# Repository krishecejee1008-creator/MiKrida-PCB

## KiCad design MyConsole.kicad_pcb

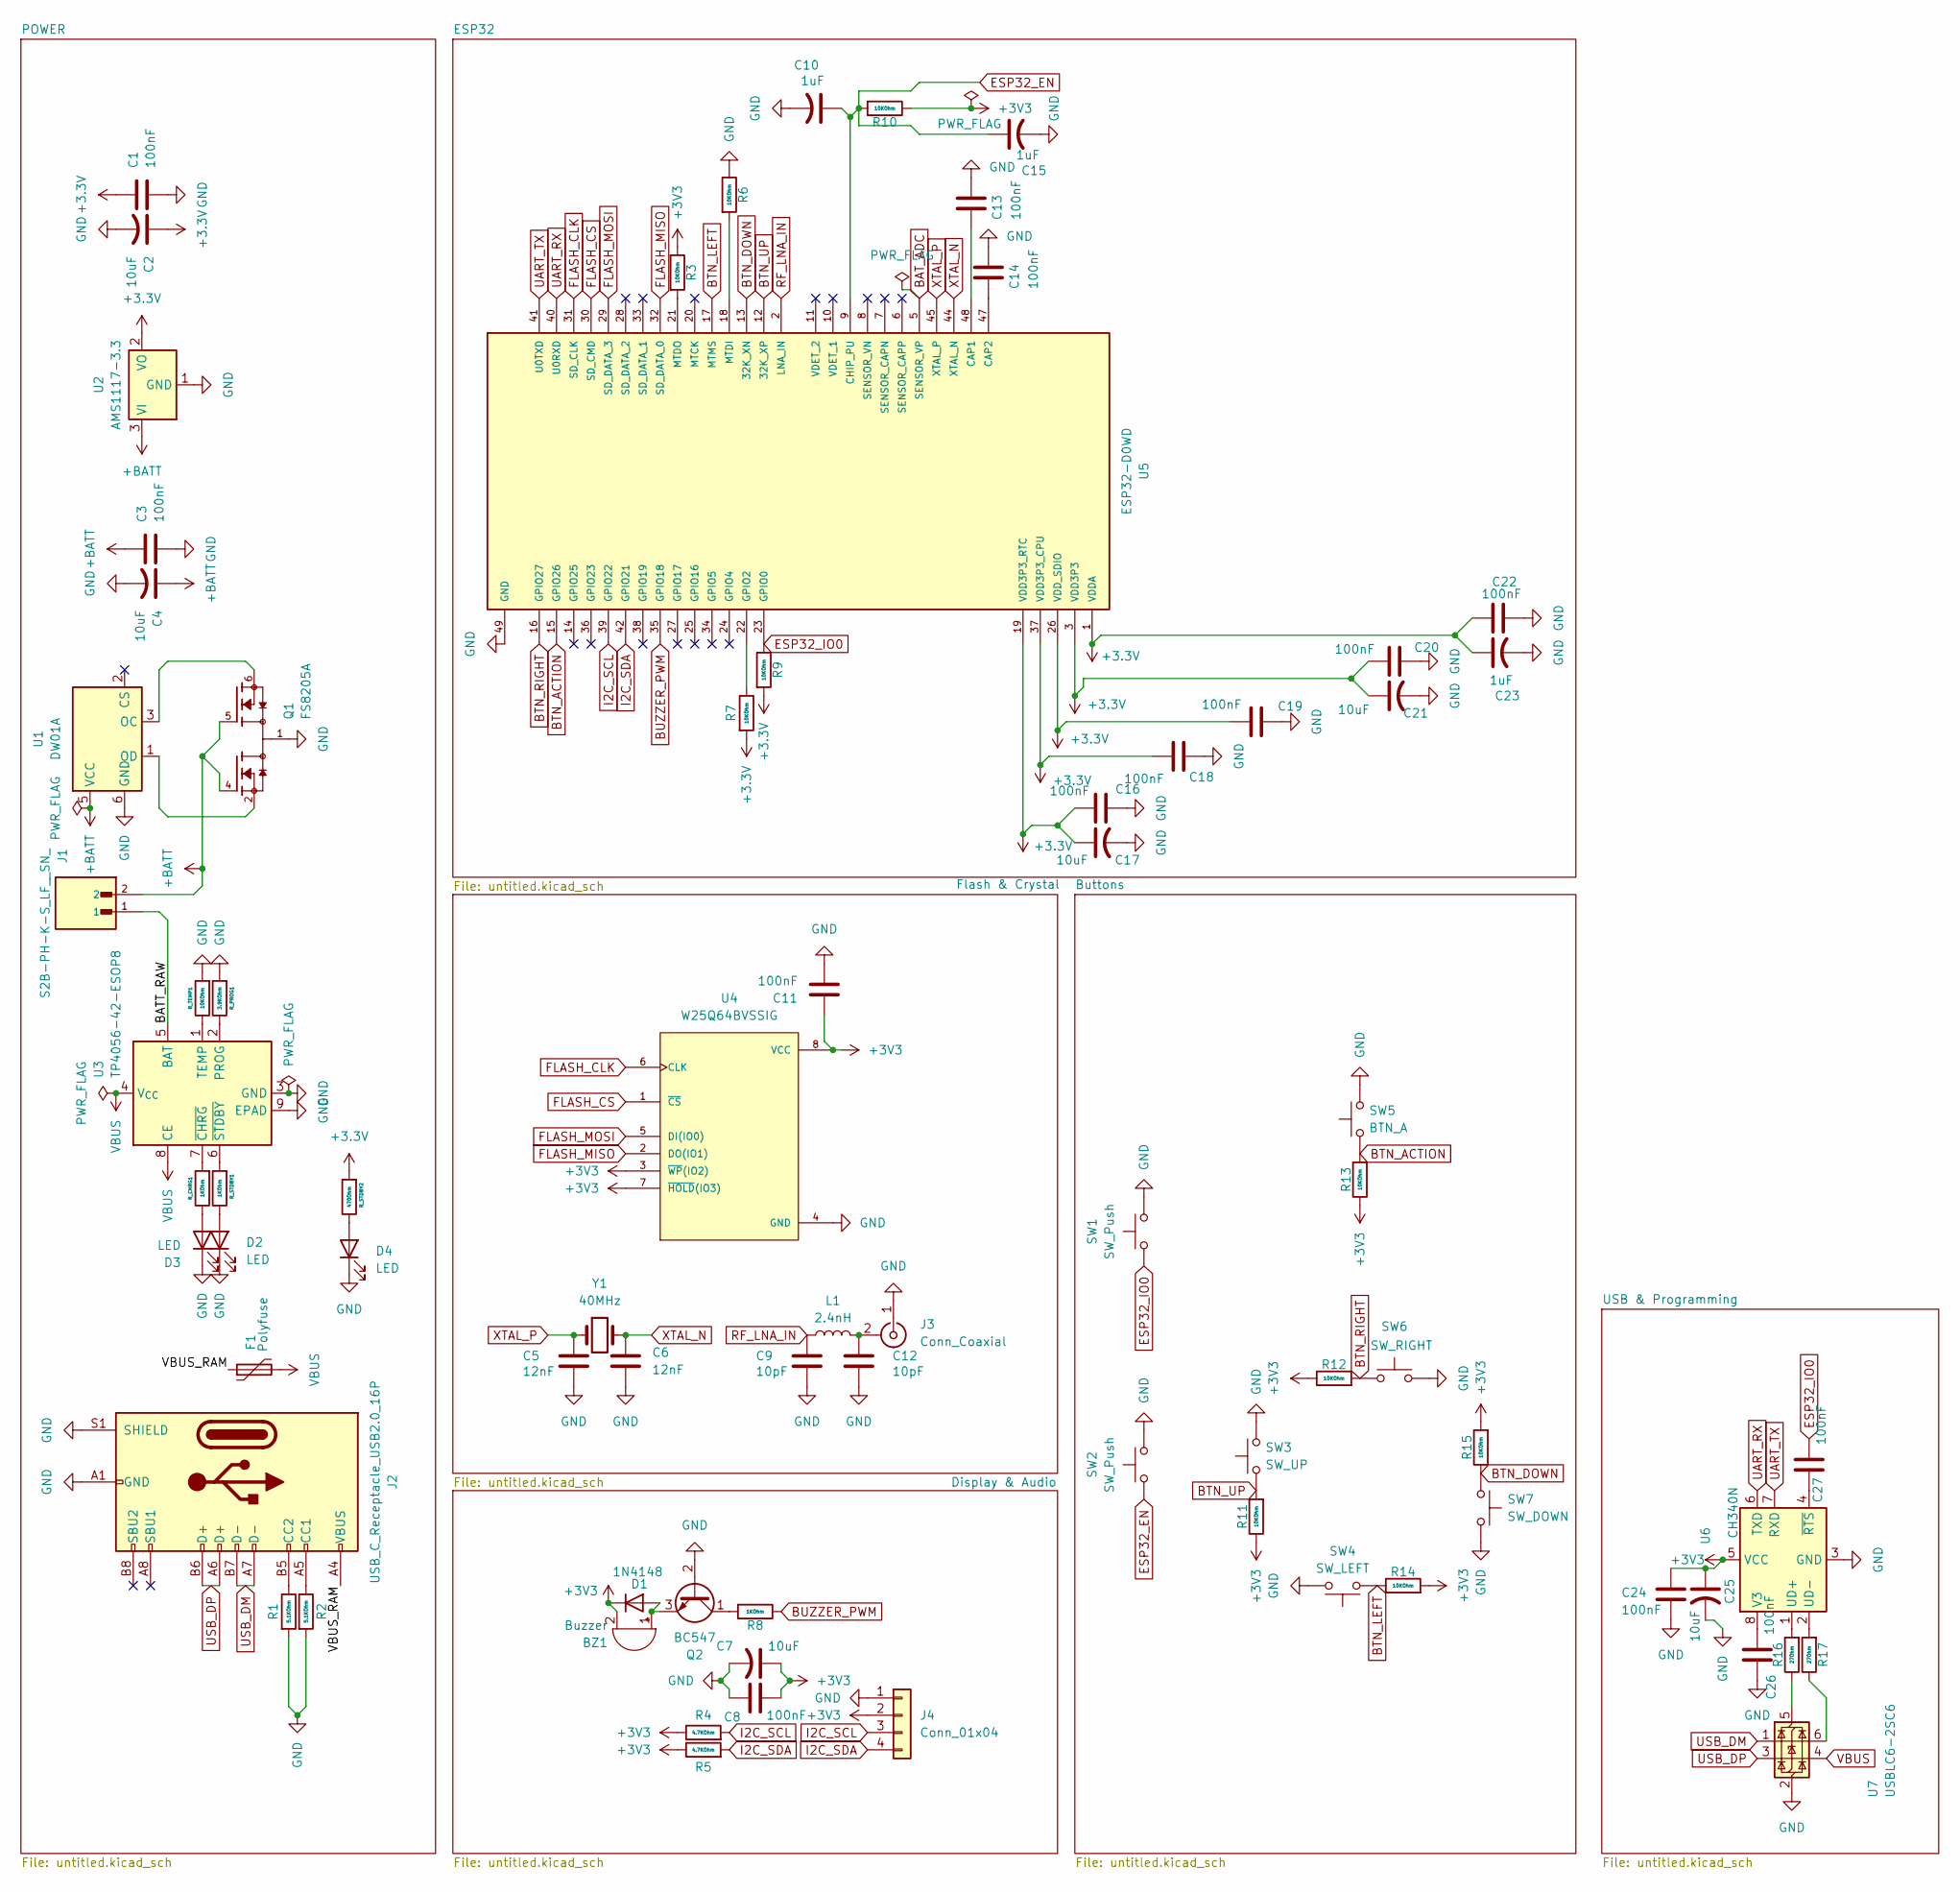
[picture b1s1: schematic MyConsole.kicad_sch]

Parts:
BZ1: Buzzer; PinHeader_1x02_P2.54mm_Vertical
C1, C3, C8, C11, C13, C14, C16, C18, C19, C20, C22, C24, C26, C27: 100nF; C_0402_1005Metric
C2, C4, C7, C17, C21, C25: 10uF; C_0805_2012Metric
C5, C6: 12nF; C_0402_1005Metric
C9, C12: 10pF; C_0402_1005Metric
C10, C15, C23: 1uF; C_0402_1005Metric
D1: 1N4148; D_SOD-123
D2, D3, D4: LED; LED_0603_1608Metric
F1: Polyfuse; Fuse_0805_2012Metric
J1: S2B-PH-K-S_LF__SN_; JST_PH_S2B-PH-K_1x02_P2.00mm_Horizontal; PARTREV R0
J2: USB_C_Receptacle_USB2.0_16P; USB_C_Receptacle_GCT_USB4085
J3: Conn_Coaxial; U.FL_Hirose_U.FL-R-SMT-1_Vertical
J4: Conn_01x04; Molex_KK-396_A-41791-0004_1x04_P3.96mm_Vertical
L1: 2.4nH; L_0402_1005Metric
Q1: FS8205A; SOT-23-6; PARTREV 1.7
Q2: BC547; SOT-23
R1, R2: 5.1KOhm; R_0402_1005Metric
R3, R6, R7, R9, R10, R11, R12, R13, R14, R15: 10KOhm; R_0402_1005Metric
R4, R5: 4.7KOhm; R_0402_1005Metric
R8: 1KOhm; R_0402_1005Metric
R16, R17: 27Ohm; R_0402_1005Metric
R_CHRG1: 1KOhm; R_0402_1005Metric
R_PROG1: 3.9KOhm; R_0402_1005Metric
R_STDBY1: 1KOhm; R_0402_1005Metric
R_STDBY2: 470Ohm; R_0402_1005Metric
R_TEMP1: 10KOhm; R_0402_1005Metric
SW1, SW2: SW_Push; SW_SPST_B3U-1000P
SW3: SW_UP; SW_SPST_B3U-1000P
SW4: SW_LEFT; SW_SPST_B3U-1000P
SW5: BTN_A; SW_SPST_B3U-1000P
SW6: SW_RIGHT; SW_SPST_B3U-1000P
SW7: SW_DOWN; SW_SPST_B3U-1000P
U1: DW01A; SOT-23-6
U2: AMS1117-3.3; SOT-223-3_TabPin2
U3: TP4056-42-ESOP8; SOIC-8-1EP_3.9x4.9mm_P1.27mm_EP2.41x3.3mm_ThermalVias
U4: W25Q64BVSSIG; SOIC127P790X216-8N
U5: ESP32-D0WD; QFN35P500X500X90-49N; PARTREV 1.7
U6: CH340N; SOP-8_3.9x4.9mm_P1.27mm
U7: USBLC6-2SC6; SOT-23-6
Y1: 40MHz; Crystal_SMD_3215-2Pin_3.2x1.5mm

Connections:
+3.3V: C1.1, C2.1, C16.1, C17.1, C18.1, C19.1, C20.1, C21.1, C22.1, C23.1, R7.2, R9.2, R_STDBY2.2, U2.2 (VO), U5.1 (VDDA), U5.3 (VDD3P3), U5.4 (VDD3P3), U5.19 (VDD3P3_RTC), U5.26 (VDD_SDIO), U5.37 (VDD3P3_CPU), U5.43 (VDDA), U5.46 (VDDA)
+3V3: BZ1.2 (-), C7.1, C8.1, C11.1, C24.1, C25.1, D1.1 (K), J4.2, R3.1, R4.1, R5.1, R10.1, R11.1, R12.1, R13.1, R14.2, R15.2, U4.3 (~WP(IO2)), U4.7 (~HOLD(IO3)), U4.8 (VCC), U6.5 (VCC)
+BATT: C3.1, C4.1, J1.2, Q1.4, Q1.5, U1.5 (VCC), U2.3 (VI)
/BATT_RAW: J1.1, U3.5 (BAT)
/VBUS_RAM: F1.1, J2.A4 (VBUS), J2.A9 (VBUS), J2.B4 (VBUS), J2.B9 (VBUS)
BAT_ADC: U5.5 (SENSOR_VP)
BTN_ACTION: R13.2, SW5.1, U5.15 (GPIO26)
BTN_DOWN: R15.1, SW7.1, U5.13 (32K_XN)
BTN_LEFT: R14.1, SW4.1, U5.17 (MTMS)
BTN_RIGHT: R12.2, SW6.1, U5.16 (GPIO27)
BTN_UP: R11.2, SW3.1, U5.12 (32K_XP)
BUZZER_PWM: R8.1, U5.35 (GPIO18)
ESP32_EN: C10.1, C15.1, R10.2, SW2.1, U5.9 (CHIP_PU)
ESP32_IO0: C27.1, R9.1, SW1.1, U5.23 (GPIO0)
FLASH_CLK: U4.6 (CLK), U5.31 (SD_CLK)
FLASH_CS: U4.1 (~CS), U5.30 (SD_CMD)
FLASH_MISO: U4.2 (DO(IO1)), U5.32 (SD_DATA_0)
FLASH_MOSI: U4.5 (DI(IO0)), U5.29 (SD_DATA_3)
GND: C1.2, C2.2, C3.2, C4.2, C5.2, C6.2, C7.2, C8.2, C9.2, C10.2, C11.2, C12.2, C13.2, C14.2, C15.2, C16.2, C17.2, C18.2, C19.2, C20.2, C21.2, C22.2, C23.2, C24.2, C25.2, C26.2, D2.1 (K), D3.1 (K), D4.1 (K), J2.A1 (GND), J2.A12 (GND), J2.B1 (GND), J2.B12 (GND), J2.S1 (SHIELD), J3.1 (In), J4.1, Q1.1, Q1.8, Q2.2 (B), R1.2, R2.2, R6.1, R_PROG1.2, R_TEMP1.2, SW1.2, SW2.2, SW3.2, SW4.2, SW5.2, SW6.2, SW7.2, U1.6 (GND), U2.1 (GND), U3.3 (GND), U3.9 (EPAD), U4.4 (GND), U5.49 (GND), U6.3 (GND), U7.2 (GND)
I2C_SCL: J4.3, R4.2, U5.39 (GPIO22)
I2C_SDA: J4.4, R5.2, U5.42 (GPIO21)
unnamed: BZ1.1 (+), D1.2 (A), Q2.3 (E)
unnamed: D2.2 (A), R_STDBY1.1
unnamed: D3.2 (A), R_CHRG1.1
unnamed: D4.2 (A), R_STDBY2.1
unnamed: J2.A5 (CC1), R2.1
unnamed: J2.B5 (CC2), R1.1
unnamed: C12.1, J3.2 (Ext), L1.2
unnamed: Q2.1 (C), R8.2
unnamed: R17.1, U7.6 (I/O1)
unnamed: Q1.6, Q1.7, U1.3 (OC)
unnamed: Q1.2, Q1.3, U1.1 (OD)
unnamed: R_PROG1.1, U3.2 (PROG)
unnamed: R_TEMP1.1, U3.1 (TEMP)
unnamed: R_CHRG1.2, U3.7 (~CHRG)
unnamed: R_STDBY1.2, U3.6 (~STDBY)
unnamed: C13.1, U5.48 (CAP1)
unnamed: C14.1, U5.47 (CAP2)
unnamed: R7.1, U5.22 (GPIO2)
unnamed: R6.2, U5.18 (MTDI)
unnamed: R3.2, U5.21 (MTDO)
unnamed: R16.2, U6.1 (UD+)
unnamed: R17.2, U6.2 (UD-)
unnamed: C26.1, U6.8 (V3)
unnamed: C27.2, U6.4 (~RTS)
unnamed: R16.1, U7.5 (VBUS)
RF_LNA_IN: C9.1, L1.1, U5.2 (LNA_IN)
UART_RX: U5.40 (U0RXD), U6.6 (TXD)
UART_TX: U5.41 (U0TXD), U6.7 (RXD)
USB_DM: J2.A7 (D-), J2.B7 (D-), U7.1 (I/O1)
USB_DP: J2.A6 (D+), J2.B6 (D+), U7.3 (I/O2)
VBUS: F1.2, U3.4 (V_{CC}), U3.8 (CE), U7.4 (I/O2)
XTAL_N: C6.1, U5.44 (XTAL_N), Y1.2
XTAL_P: C5.1, U5.45 (XTAL_P), Y1.1

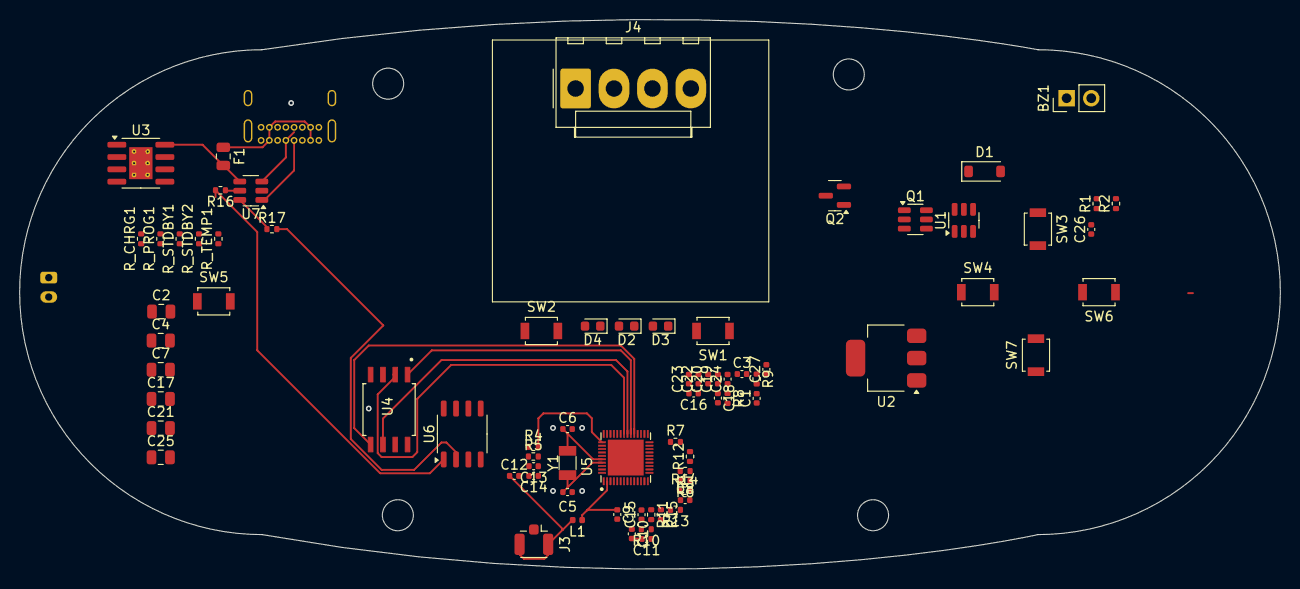
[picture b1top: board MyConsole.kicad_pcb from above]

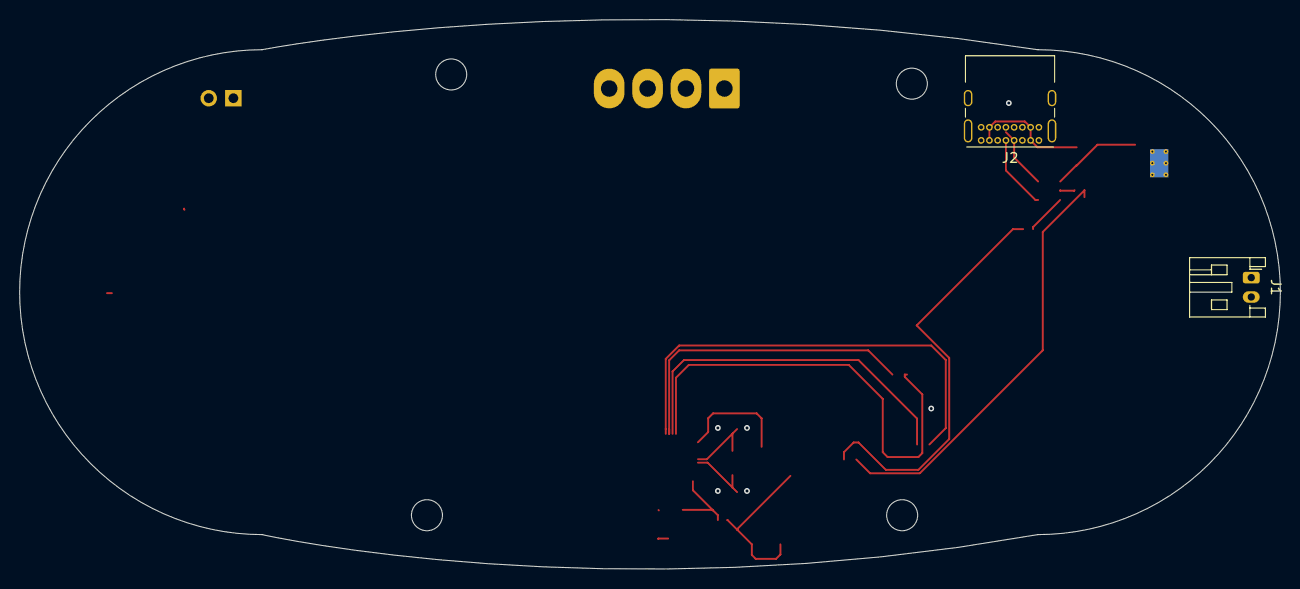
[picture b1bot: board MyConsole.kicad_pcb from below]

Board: 4 copper layers, 130.0 x 56.6 mm, 77 parts (2 on the bottom side), 53 nets.
